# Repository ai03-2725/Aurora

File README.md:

# Aurora

#### In light of recent claims that I am 100% liable for any of my open source PCBs, I am adding this disclaimer.
#### I provide these PCBs as a reference for designing keyboard PCBs. Using them within your projects will require a will to do research of one's own and to learn the workings of them, potentially fixing issues if they exist.
# I provide these PCBs without liability and without any guarantees regarding functionality, as expressed in the MIT license under which all of these PCBs are licensed.

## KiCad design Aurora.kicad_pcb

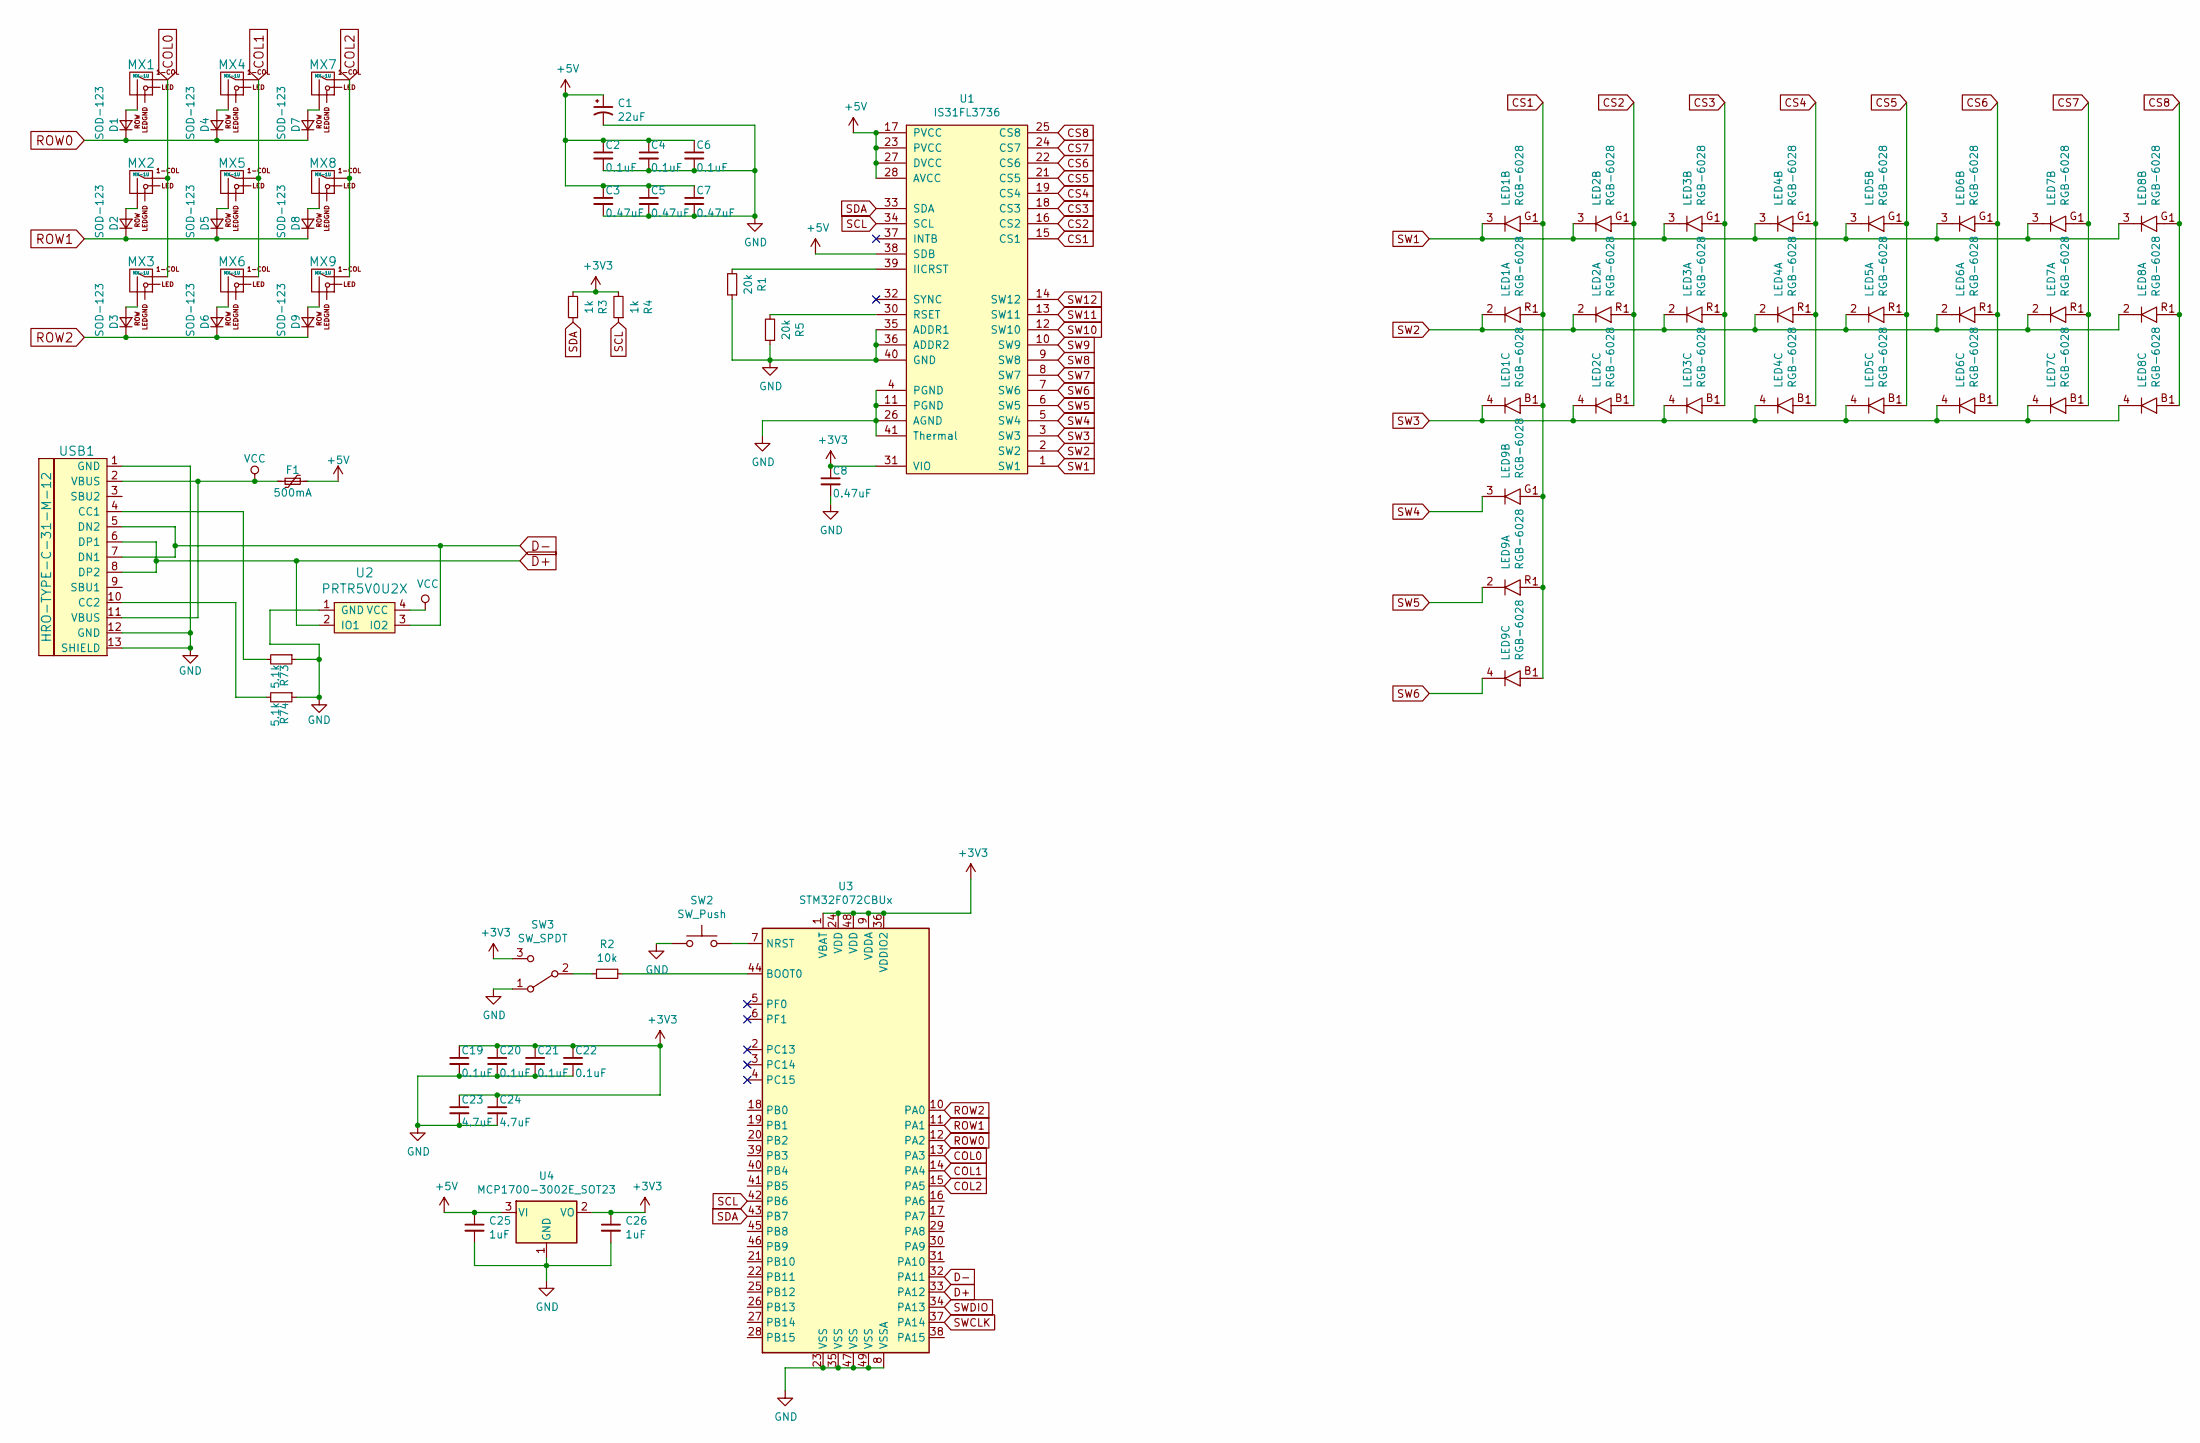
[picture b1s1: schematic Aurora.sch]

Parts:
C1: 22uF; CP_Tantalum_Case-T_EIA-3528-12_Reflow
C2, C4, C6, C19, C20, C21, C22: 0.1uF; C_0603
C3, C5, C7, C8: 0.47uF; C_0603
C23, C24: 4.7uF; C_0603
C25, C26: 1uF; C_0603
D1, D2, D3, D4, D5, D6, D7, D8, D9: SOD-123; D_SOD-323
F1: 500mA; Fuse_SMD1206_Reflow
LED1, LED2, LED3, LED4, LED5, LED6, LED7, LED8, LED9: RGB-6028
MX1, MX2, MX3, MX4, MX5, MX6, MX7, MX8, MX9: MX-1U; MXOnly-1U-Hotswap
R1, R5: 20k; R_0603
R2: 10k; R_0603
R3, R4: 1k; R_0603
R73, R74: 5.1k; R_0603
SW2: SW_Push; SW_SPST_SKQG
SW3: SW_SPDT; SW_SPDT_PCM12
U1: IS31FL3736; QFN-40-1EP_5x5mm_Pitch0.4mm
U2: PRTR5V0U2X; SOT143B
U3: STM32F072CBUx; QFN-48-1EP_7x7mm_Pitch0.5mm
U4: MCP1700-3002E_SOT23; SOT-23
USB1: HRO-TYPE-C-31-M-12; HRO-TYPE-C-31-M-12-Assembly

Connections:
+3V3: C8.1, C19.1, C20.1, C21.1, C22.1, C23.1, C24.1, C26.1, R3.2, R4.2, SW3.3 (C), U1.31 (VIO), U3.1 (VBAT), U3.9 (VDDA), U3.24 (VDD), U3.36 (VDDIO2), U3.48 (VDD), U4.2 (VO)
+5V: C1.1, C2.1, C3.1, C4.1, C5.1, C6.1, C7.1, C25.1, F1.1, U1.17 (PVCC), U1.23 (PVCC), U1.27 (DVCC), U1.28 (AVCC), U1.38 (SDB), U4.3 (VI)
COL0: MX1.1 (COL), MX2.1 (COL), MX3.1 (COL), U3.13 (PA3)
COL1: MX4.1 (COL), MX5.1 (COL), MX6.1 (COL), U3.14 (PA4)
COL2: MX7.1 (COL), MX8.1 (COL), MX9.1 (COL), U3.15 (PA5)
CS1: LED1.1 (A), LED9.1 (A), U1.15 (CS1)
CS2: LED2.1 (A), U1.16 (CS2)
CS3: LED3.1 (A), U1.18 (CS3)
CS4: LED4.1 (A), U1.19 (CS4)
CS5: LED5.1 (A), U1.21 (CS5)
CS6: LED6.1 (A), U1.22 (CS6)
CS7: LED7.1 (A), U1.24 (CS7)
CS8: LED8.1 (A), U1.25 (CS8)
D+: U2.2 (IO1), U3.33 (PA12), USB1.6 (DP1), USB1.8 (DP2)
D-: U2.3 (IO2), U3.32 (PA11), USB1.5 (DN2), USB1.7 (DN1)
GND: C1.2, C2.2, C3.2, C4.2, C5.2, C6.2, C7.2, C8.2, C19.2, C20.2, C21.2, C22.2, C23.2, C24.2, C25.2, C26.2, R1.1, R5.1, R73.1, R74.1, SW2.1, SW3.1 (A), U1.4 (PGND), U1.11 (PGND), U1.26 (AGND), U1.35 (ADDR1), U1.36 (ADDR2), U1.40 (GND), U1.41 (Thermal), U2.1 (GND), U3.8 (VSSA), U3.23 (VSS), U3.35 (VSS), U3.47 (VSS), U3.49 (VSS), U4.1 (GND), USB1.1 (GND), USB1.12 (GND), USB1.13 (SHIELD)
unnamed: D1.2 (A), MX1.2 (ROW)
unnamed: D2.2 (A), MX2.2 (ROW)
unnamed: D3.2 (A), MX3.2 (ROW)
unnamed: D4.2 (A), MX4.2 (ROW)
unnamed: D5.2 (A), MX5.2 (ROW)
unnamed: D6.2 (A), MX6.2 (ROW)
unnamed: D7.2 (A), MX7.2 (ROW)
unnamed: D8.2 (A), MX8.2 (ROW)
unnamed: D9.2 (A), MX9.2 (ROW)
unnamed: R1.2, U1.39 (IICRST)
unnamed: R2.1, U3.44 (BOOT0)
unnamed: R2.2, SW3.2 (B)
unnamed: R5.2, U1.30 (RSET)
unnamed: R73.2, USB1.4 (CC1)
unnamed: R74.2, USB1.10 (CC2)
unnamed: SW2.2, U3.7 (NRST)
ROW0: D1.1 (K), D4.1 (K), D7.1 (K), U3.12 (PA2)
ROW1: D2.1 (K), D5.1 (K), D8.1 (K), U3.11 (PA1)
ROW2: D3.1 (K), D6.1 (K), D9.1 (K), U3.10 (PA0)
SCL: R4.1, U1.34 (SCL), U3.42 (PB6)
SDA: R3.1, U1.33 (SDA), U3.43 (PB7)
SW1: LED1.3 (C), LED2.3 (C), LED3.3 (C), LED4.3 (C), LED5.3 (C), LED6.3 (C), LED7.3 (C), LED8.3 (C), U1.1 (SW1)
SW2: LED1.2 (C), LED2.2 (C), LED3.2 (C), LED4.2 (C), LED5.2 (C), LED6.2 (C), LED7.2 (C), LED8.2 (C), U1.2 (SW2)
SW3: LED1.4 (C), LED2.4 (C), LED3.4 (C), LED4.4 (C), LED5.4 (C), LED6.4 (C), LED7.4 (C), LED8.4 (C), U1.3 (SW3)
SW4: LED9.3 (C), U1.5 (SW4)
SW5: LED9.2 (C), U1.6 (SW5)
SW6: LED9.4 (C), U1.7 (SW6)
SW7: U1.8 (SW7)
SW8: U1.9 (SW8)
SW9: U1.10 (SW9)
SW10: U1.12 (SW10)
SW11: U1.13 (SW11)
SW12: U1.14 (SW12)
SWCLK: U3.37 (PA14)
SWDIO: U3.34 (PA13)
VCC: F1.2, U2.4 (VCC), USB1.2 (VBUS), USB1.11 (VBUS)

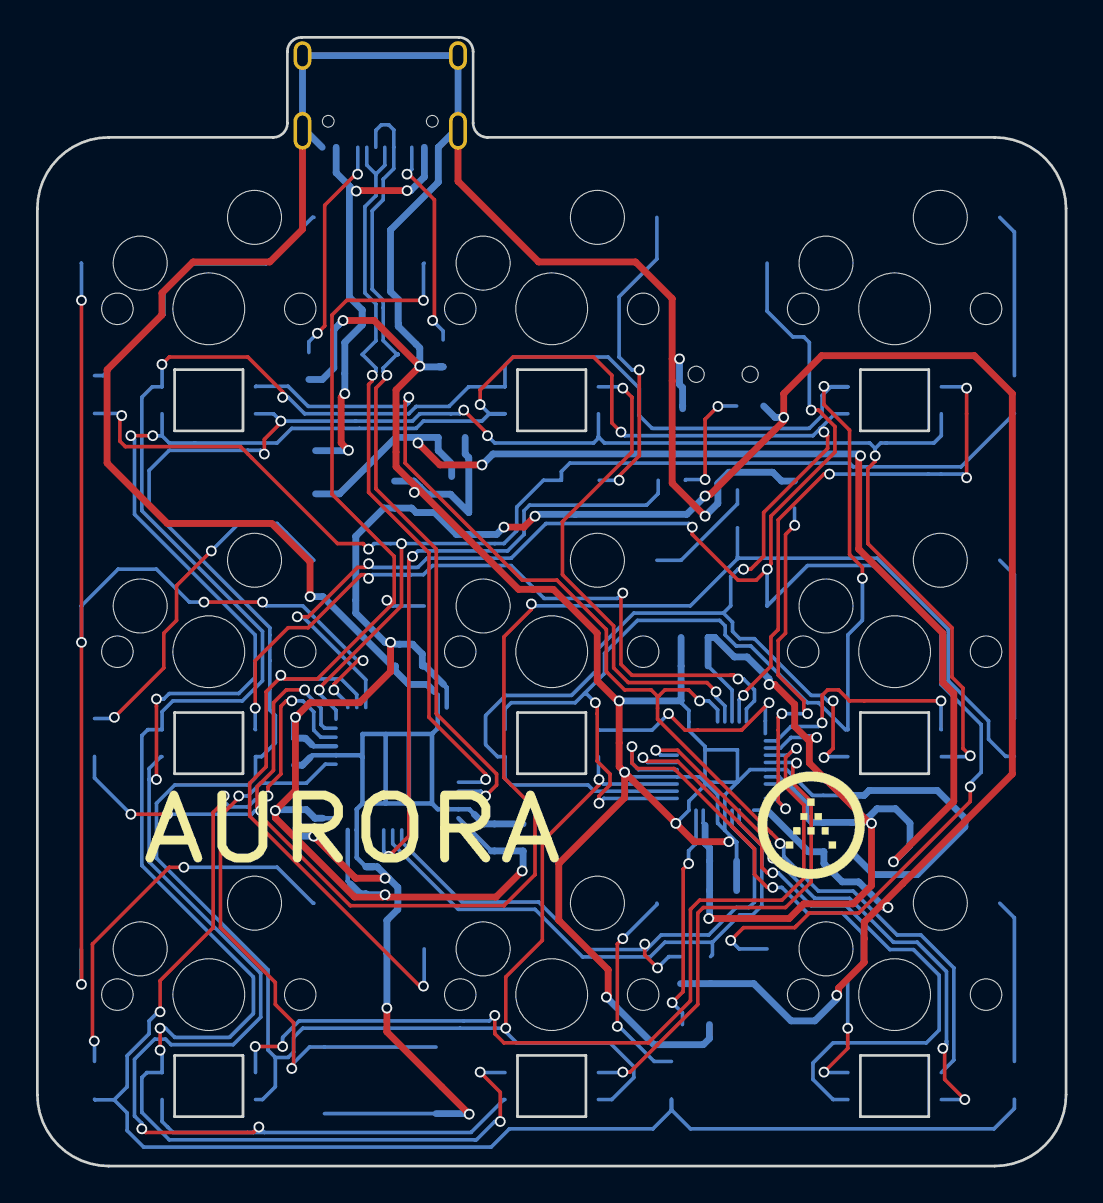
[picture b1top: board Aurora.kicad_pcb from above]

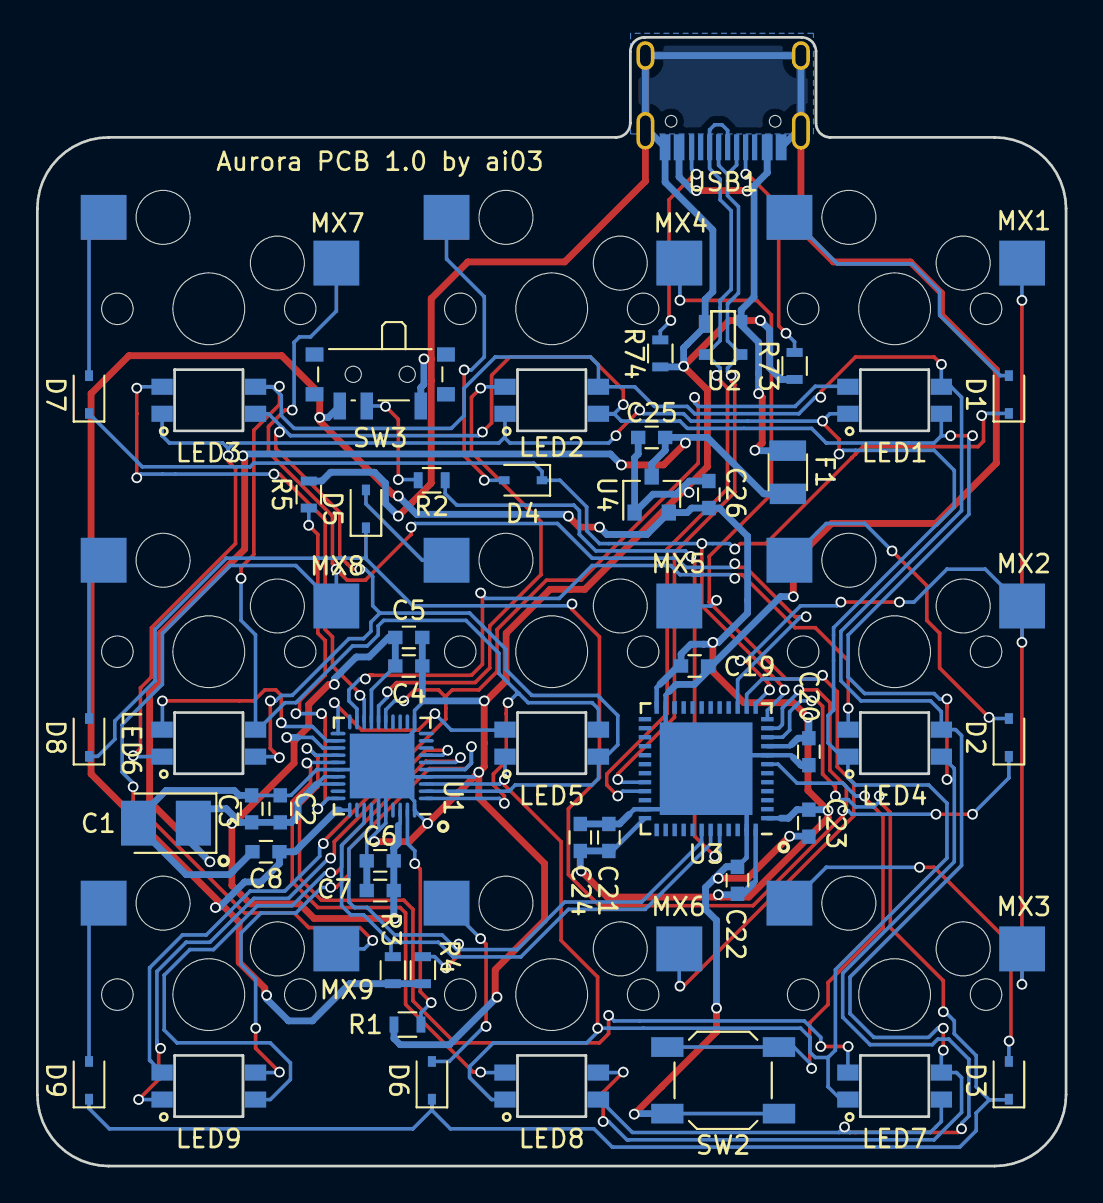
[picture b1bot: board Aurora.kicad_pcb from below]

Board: 2 copper layers, 57.1 x 62.7 mm, 58 parts (49 on the bottom side), 44 nets.

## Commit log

2019-03-09 Copy in Voyager40-arm files
2019-03-09 Update submod
2019-03-09 Progress
2019-03-09 Update submods
2019-03-10 Rename project
2019-03-10 Update submodules
2019-03-11 progress save
2019-03-11 Update submodule
2019-03-11 Begin replace LED MCU
2019-03-11 Route it
2019-03-11 Route PCB
2019-03-11 Tune-up
2019-03-11 Further tuning
